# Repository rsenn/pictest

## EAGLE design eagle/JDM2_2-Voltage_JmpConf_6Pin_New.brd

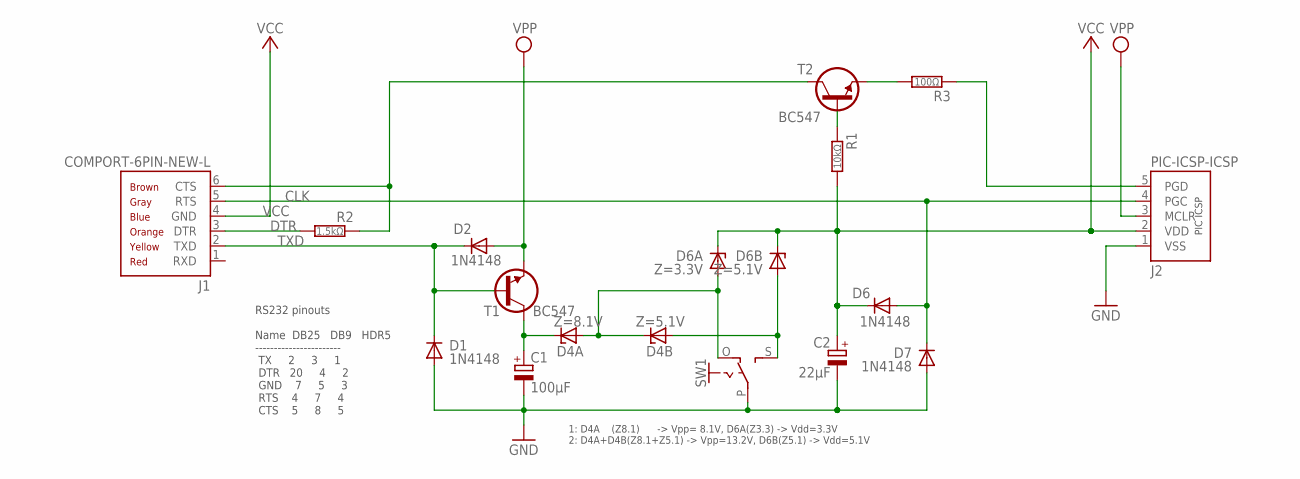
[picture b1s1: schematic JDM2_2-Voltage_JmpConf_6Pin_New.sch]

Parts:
C1: 100μF; E2,5-5/V
C2: 22μF; E2.5-4/V
D1, D6: 1N4148; DO34-5V
D2: 1N4148; DO34-5
D4A: Z=8.1V; DO34Z5
D4B: Z=5.1V; DO34Z5
D6A: Z=3.3V; DO34Z7V
D6B: Z=5.1V; DO34Z7V
D7: 1N4148; DO34-7V
J1: COMPORT-6PIN-NEW-L; RS232-6PIN-NEW-L
J2: PIC-ICSP-ICSP; PIC-ICSP
R1: 10kΩ; 0202/7-V
R2: 1.5kΩ; 0202/7-V
R3: 100Ω; 0202/7
SW1: SL-SW-1P-2T-JPSW; JPSW-1P2T
T1, T2: BC547; TO92-CBE

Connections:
/MCLR: D2.A, J2.3 (MCLR), T1.E
CLK: D6.A, D7.C, J1.5 (RTS), J2.4 (PGC)
CTS: J1.6 (CTS), R2.1, T2.C
DATA: R3.2, T2.E
DTR: J1.3 (DTR), R2.2
GND: C1.-, C2.-, D1.A, D7.A, J2.1 (VSS), SW1.P
unnamed: R1.1, T2.B
unnamed: D4B.A, D6B.A, SW1.S
unnamed: D4A.A, D4B.C, D6A.A, SW1.O
PGD: J2.5 (PGD), R3.1
TXD: D1.C, D2.C, J1.2 (TXD), T1.B
VCC: C2.+, D6.C, D6A.C, D6B.C, J1.4 (GND), J2.2 (VDD), R1.2
VPP: C1.+, D4A.C, T1.C

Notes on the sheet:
RS232 pinouts Name DB25 DB9 HDR5 ----------------------- TX 2 3 1 DTR 20 4 2 GND 7 5 3 RTS 4 7 4 CTS 5 8 5
1: D4A (Z8.1) -> Vpp= 8.1V, D6A(Z3.3) -> Vdd=3.3V 2: D4A+D4B(Z8.1+Z5.1) -> Vpp=13.2V, D6B(Z5.1) -> Vdd=5.1V

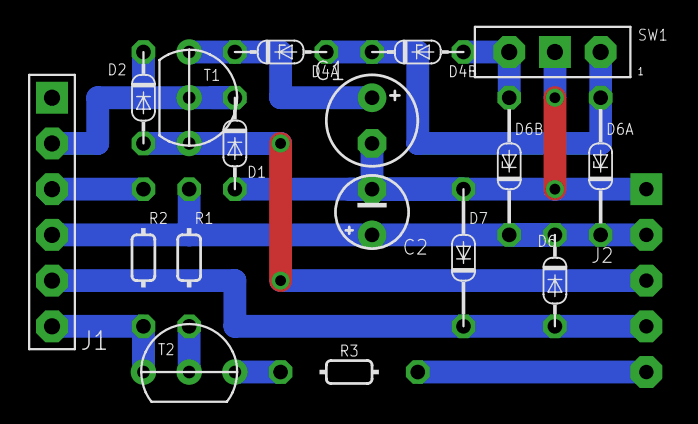
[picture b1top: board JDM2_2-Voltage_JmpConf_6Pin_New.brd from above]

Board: 2 copper layers, 18 parts (0 on the bottom side), 13 nets.

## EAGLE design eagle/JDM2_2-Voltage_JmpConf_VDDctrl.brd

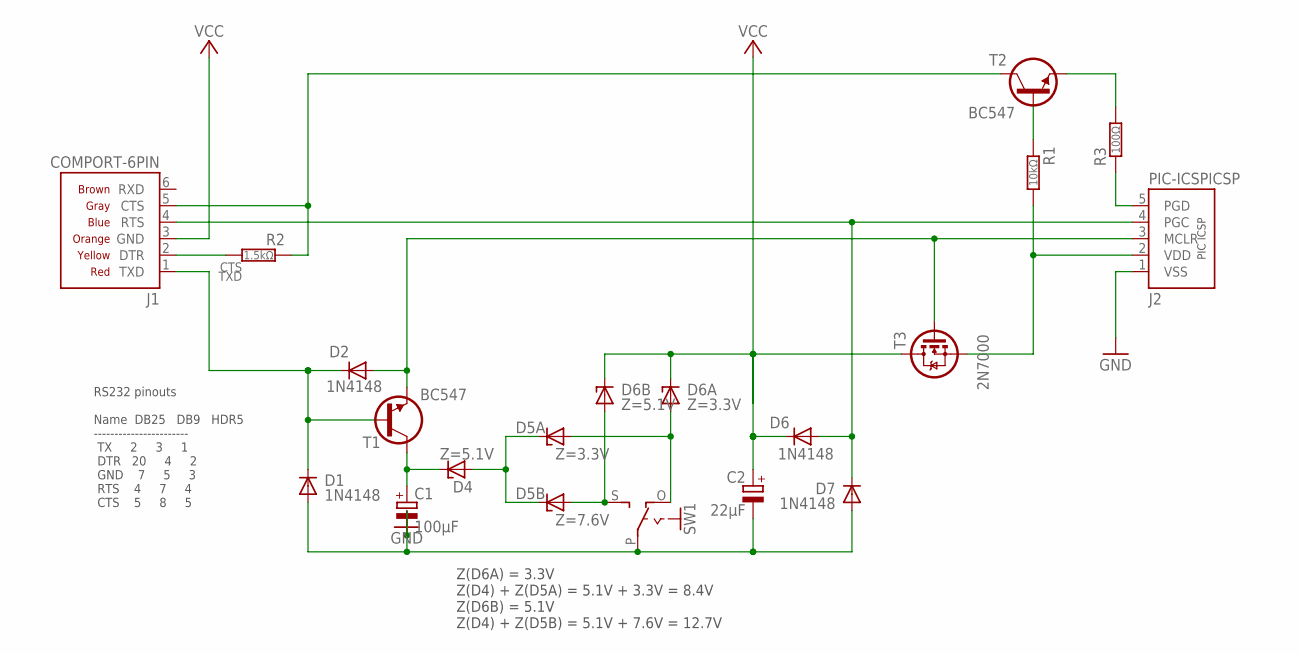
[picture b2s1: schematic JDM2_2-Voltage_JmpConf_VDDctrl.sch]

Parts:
C1: 100μF; E2,5-5/V
C2: 22μF; E2.5-4/V
D1, D2: 1N4148; DO34-5
D4: Z=5.1V; DO34Z7
D5A: Z=3.3V; DO34Z7
D5B: Z=7.6V; DO34Z7
D6: 1N4148; DO34-10V
D6A: Z=3.3V; DO34Z7V
D6B: Z=5.1V; DO34Z7V
D7: 1N4148; DO34-7V
J1: COMPORT-6PIN; RS232-6PIN
J2: PIC-ICSPICSP; PIC-ICSP
R1: 10kΩ; 0202/7-V
R2: 1.5kΩ; 0202/7-V
R3: 100Ω; 0202/7
SW1: SL-SW-1P-2T-JPSW; JPSW-1P2T
T1, T2: BC547; TO92-CBE
T3: 2N7000; TO92

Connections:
/MCLR: D2.A, J2.3 (MCLR), T1.E, T3.2 (G)
CLK: D6.A, D7.C, J1.4 (RTS), J2.4 (PGC)
CTS: J1.5 (CTS), R2.1, T2.C
DATA: R3.2, T2.E
GND: C1.-, C2.-, D1.A, D7.A, J2.1 (VSS), SW1.P
unnamed: R1.1, T2.B
unnamed: D5A.A, D6A.A, SW1.O
unnamed: D5B.A, D6B.A, SW1.S
unnamed: D4.A, D5A.C, D5B.C
unnamed: J2.2 (VDD), R1.2, T3.1 (S)
unnamed: J1.2 (DTR), R2.2
PGD: J2.5 (PGD), R3.1
TXD: D1.C, D2.C, J1.1 (TXD), T1.B
VCC: C2.+, D6.C, D6A.C, D6B.C, J1.3 (GND), T3.3 (D)
VPP: C1.+, D4.C, T1.C

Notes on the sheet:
RS232 pinouts Name DB25 DB9 HDR5 ----------------------- TX 2 3 1 DTR 20 4 2 GND 7 5 3 RTS 4 7 4 CTS 5 8 5
Z(D6A) = 3.3V Z(D4) + Z(D5A) = 5.1V + 3.3V = 8.4V Z(D6B) = 5.1V Z(D4) + Z(D5B) = 5.1V + 7.6V = 12.7V

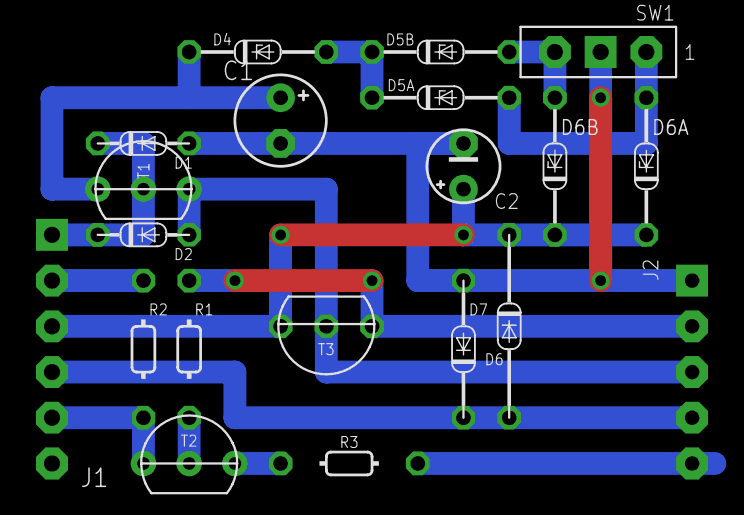
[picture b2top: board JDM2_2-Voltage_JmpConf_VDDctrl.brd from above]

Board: 2 copper layers, 20 parts (0 on the bottom side), 15 nets.
